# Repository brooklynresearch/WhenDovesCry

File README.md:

# ToniDove
Robotic Control and Communication.  

## OSC Messaging
The OSC messaging protocol to control the servos.
The current two messages to control the shoulder of the robot arm are `/sPitch` and `/sRoll`.  The Pitch message controlling the base rotation (single servo), and the Roll message controlling the swing angle (two servos).  Each message requires two integer arguments.  
### Arguments
`servoPosition` which has a range of 0 - 2047
 `servoSpeed` which has a range of 1 - inf. 
 `servoSpeed` is roughly in milliseconds and the value given is the amount of time you gave to go from currentPosition to the previously supplied servePosition (i.e. the larger the value given, the slower it will move)
### OSC Message Orientation
```{r, engine='bash', count_lines}
/sPitch servoPosition servoSpeed
/sRoll servoPosition servoSpeed
```
### OSC Example
```{r, engine='bash', count_lines}
/sPitch 512 18
/sRoll 1024 100
```
Current IP address is 192.168.0.200
Current listening PORT is 12345

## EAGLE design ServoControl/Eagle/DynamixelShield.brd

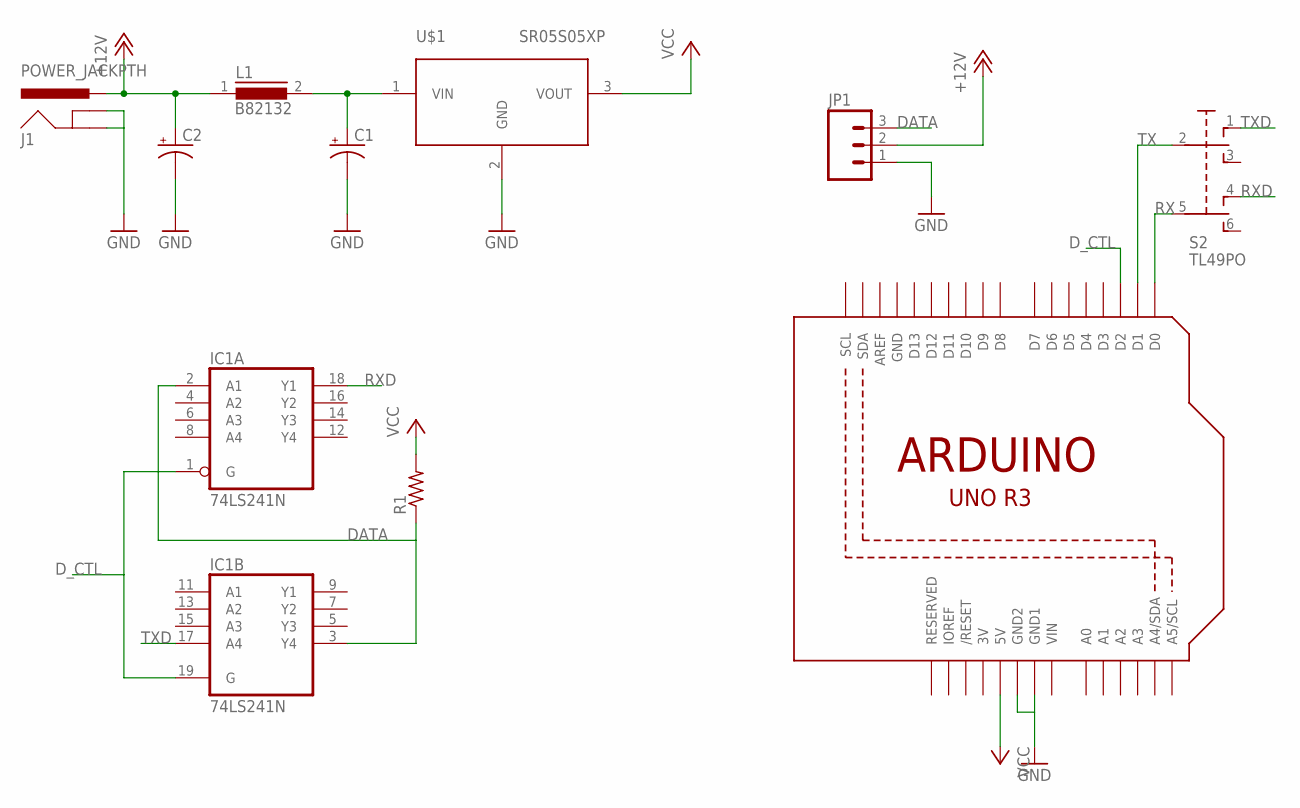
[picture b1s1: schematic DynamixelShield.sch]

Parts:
C1, C2: CPOL-USE3.5-10; E3,5-10
IC1: 74LS241N; DIL20
J1: POWER_JACKPTH; POWER_JACK_PTH
JP1: M031X03_NO_SILK; 1X03_NO_SILK
L1: B82132; SUKW2-22
R1: R-US_0204/7; 0204/7
S2: TL49PO; TL4XPO
U1: ARDUINOR3-DIMENSION; ARDUINOR3
U$1: SR05S05XP; XP_3PIN_SIP

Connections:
3V: U1.3V
+12V: C2.+, J1.PWR, JP1.2, L1.1
DATA: IC1.2 (A1), IC1.3 (Y4), JP1.3, R1.1
D_CTL: IC1.1 (G), IC1.19 (G), U1.D2
GND: C1.-, C2.-, IC1.10 (GND), J1.GND, J1.GNDBREAK, JP1.1, U1.GND, U1.GND1, U1.GND2, U$1.2 (GND)
unnamed: C1.+, L1.2, U$1.1 (VIN)
RX: S2.5 (P1), U1.D0
RXD: IC1.18 (Y1), S2.4 (O1)
TX: S2.2, U1.D1
TXD: IC1.17 (A4), S2.1 (O)
VCC: IC1.20 (VCC), R1.2, U1.5V, U$1.3 (VOUT)
VIN: U1.VIN

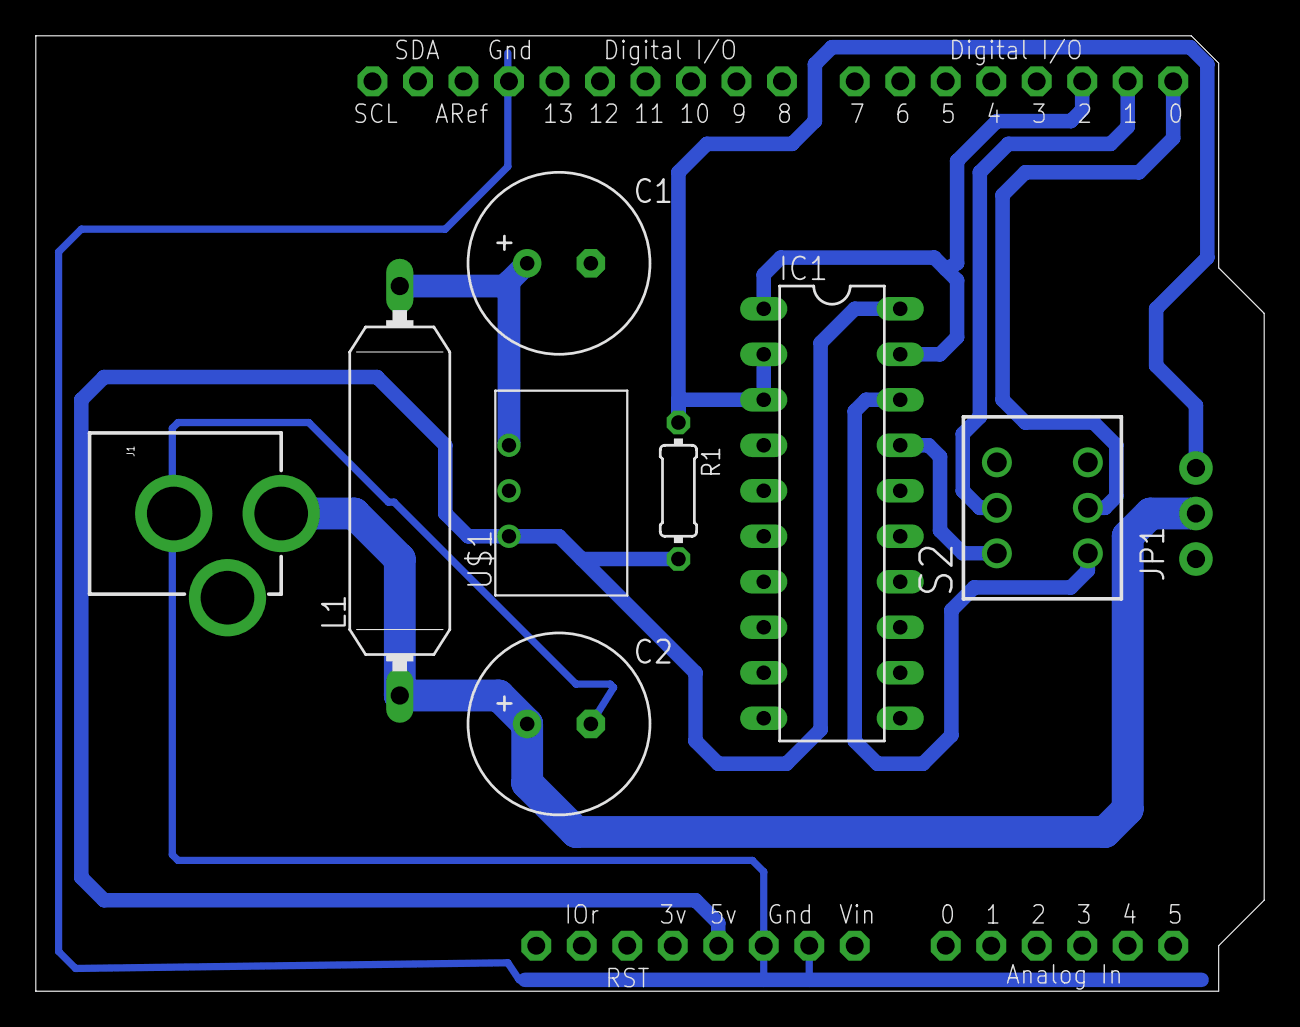
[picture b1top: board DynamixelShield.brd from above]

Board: 2 copper layers, 68.6 x 53.3 mm, 10 parts (0 on the bottom side), 10 nets.

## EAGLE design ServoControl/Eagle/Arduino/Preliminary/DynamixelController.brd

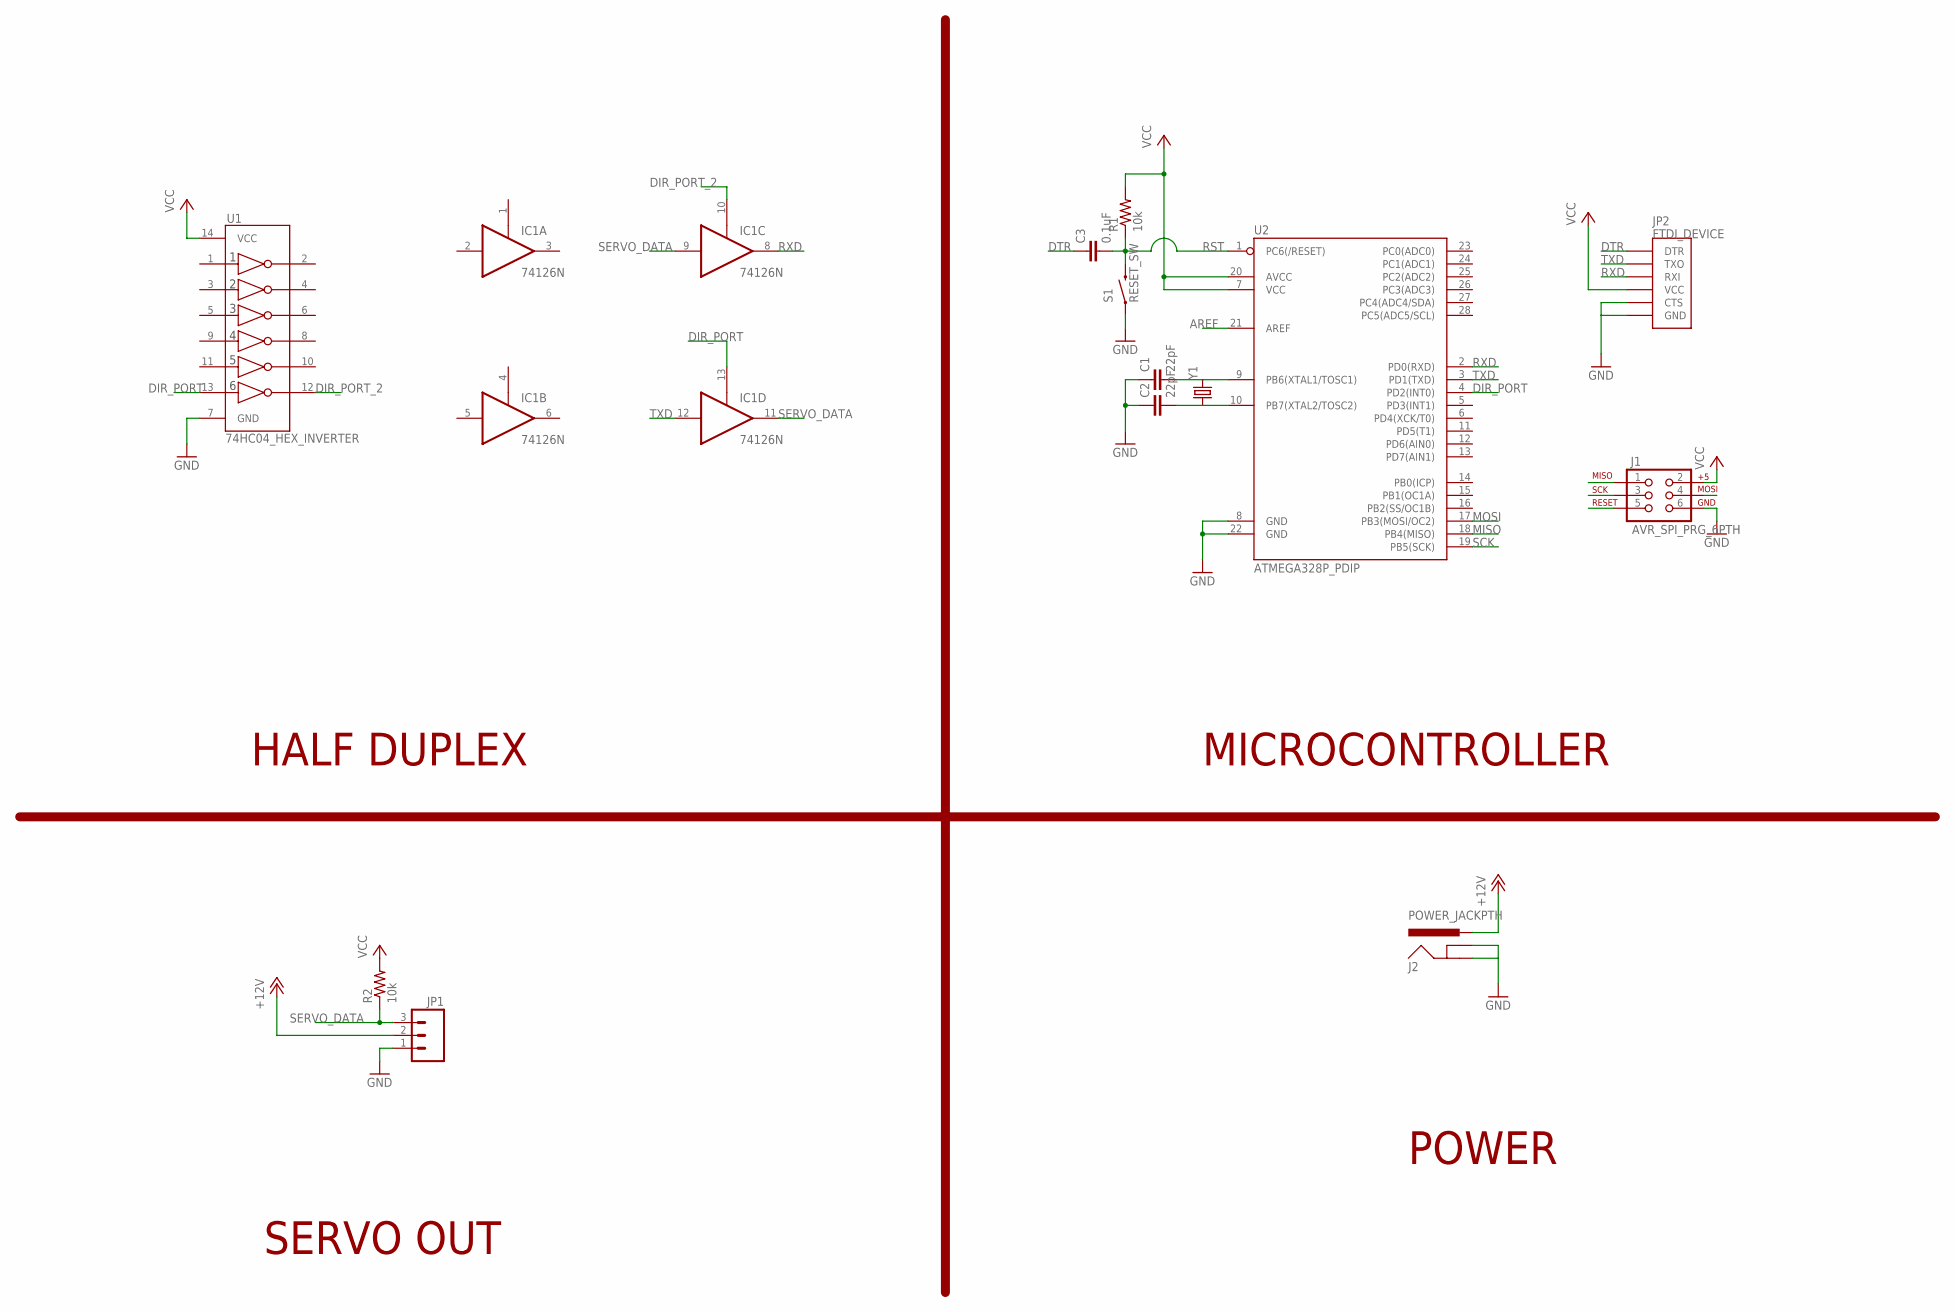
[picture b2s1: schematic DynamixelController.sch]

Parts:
C1, C2: 22pF; C050-024X044
C3: 0.1uF; C050-024X044
IC1: 74126N; DIL14
J1: AVR_SPI_PRG_6PTH; 2X3
J2: POWER_JACKPTH; POWER_JACK_PTH
JP1: M03POLAR; MOLEX-1X3
JP2: FTDI_DEVICE; FTDI_DEVICE_SIDE
R1, R2: 10k; 0207/7
S1: RESET_SW; TACTILE-PTH
U1: 74HC04_HEX_INVERTER; DIL14
U2: ATMEGA328P_PDIP; DIL28-3
Y1: CRYSTALHC49US; HC49US

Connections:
+12V: J2.PWR, JP1.2
AREF: U2.21 (AREF)
DIR_PORT: IC1.13 (OE), U1.13 (6A), U2.4 (PD2(INT0))
DIR_PORT_2: IC1.10 (OE), U1.12 (6Y)
DTR: C3.1, JP2.P$1 (DTR)
GND: C1.1, C2.1, IC1.7 (GND), J1.6, J2.GND, J2.GNDBREAK, JP1.1, JP2.P$5 (CTS), JP2.P$6 (GND), S1.1, U1.7 (GND), U2.8 (GND), U2.22 (GND)
MISO: J1.1, U2.18 (PB4(MISO))
MOSI: J1.4, U2.17 (PB3(MOSI/OC2))
unnamed: C1.2, U2.9 (PB6(XTAL1/TOSC1)), Y1.2
unnamed: C2.2, U2.10 (PB7(XTAL2/TOSC2)), Y1.1
RST: C3.2, J1.5, R1.1, S1.3 (2), U2.1 (PC6(/RESET))
RXD: IC1.8 (O), JP2.P$3 (RXI), U2.2 (PD0(RXD))
SCK: J1.3, U2.19 (PB5(SCK))
SERVO_DATA: IC1.9 (I), IC1.11 (O), JP1.3, R2.1
TXD: IC1.12 (I), JP2.P$2 (TXO), U2.3 (PD1(TXD))
VCC: IC1.14 (VCC), J1.2, JP2.P$4 (VCC), R1.2, R2.2, U1.14 (VCC), U2.7 (VCC), U2.20 (AVCC)

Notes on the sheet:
MICROCONTROLLER
HALF DUPLEX
SERVO OUT
POWER

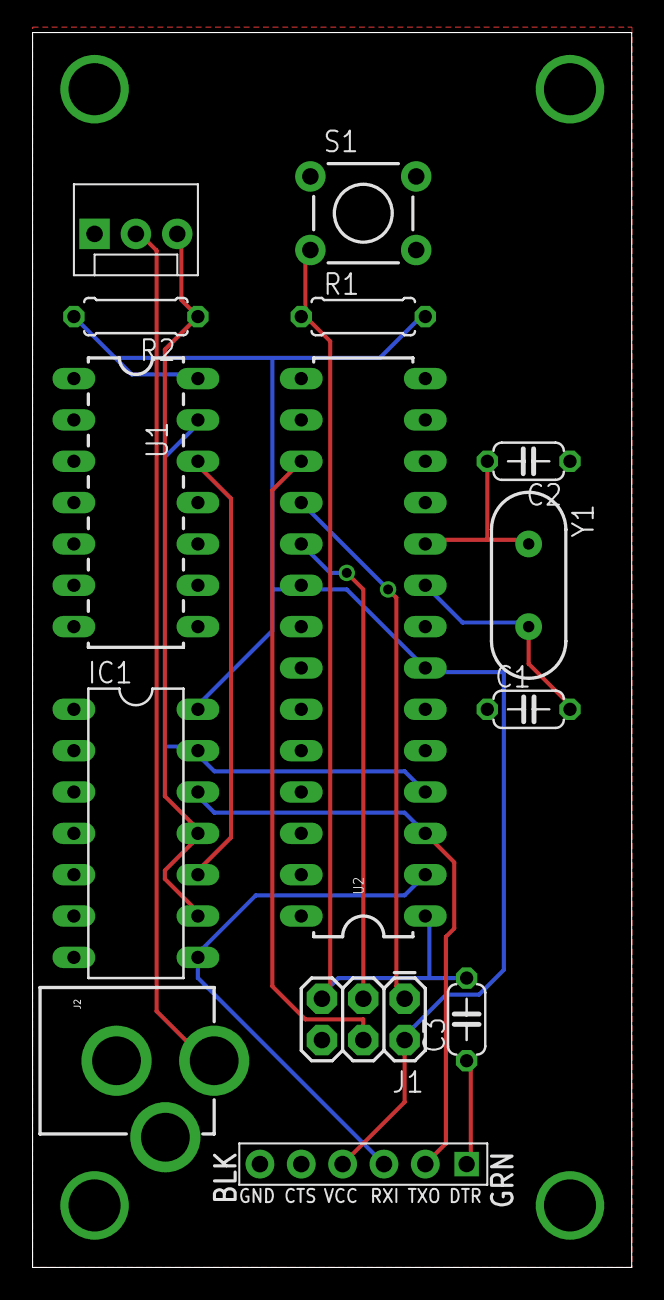
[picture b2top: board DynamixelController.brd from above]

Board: 2 copper layers, 36.8 x 75.9 mm, 14 parts (0 on the bottom side), 15 nets.

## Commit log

2015-06-04 Initial Push
    Initial Arduino sketch just for testing Dynamixel Servos. By no means
    complete, just a starting point.
2015-06-04 Preliminary Board Designs
    Preliminary schematics and layout for servo control using atmega328
    (Arduino). Still need better power distribution, sensors inputs, and
    limit switch inputs.
2015-06-09 Easing Library Uploaded
    Used a servo easing library and ported it for dynamixels servos
    specifically. Added an example to move up to three servos from a list
    of positions.
2015-10-08 OSC Update
    Added initial OSC Firmware code, with necessary libraries, and readme
    file. Also included the eagle file to print the Arduino shield for
    controlling the Dynamixels.

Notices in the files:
parts and their libraries:
SparkFun-DigitalIC: Licensing: CC v3.0 Share-Alike You are welcome to use this library for commercial purposes.
